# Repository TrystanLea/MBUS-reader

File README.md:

# M-Bus reader
to go with [emonTX](https://github.com/openenergymonitor/emontx3)

Part of [OpenEnergyMonitor.org](https://openenergymonitor.org) project.

This board allows you to read data from M-bus module in the heat meter. 

The Meter-Bus(M-Bus) is a low cost bus system for remote reading and powering utility meters. It is also the European Standard. 

Circuit diagram used is from [here](https://github.com/rscada/libmbus/tree/master/hardware).

The 34V is provided to the circuit through a [DC to DC voltage step up boost converter](http://www.ebay.co.uk/itm/XL6009-DC-DC-Voltage-Step-Up-Boost-Converter-replace-LM2577-3-32v-input-UK-Fast-/400858208676). 

## Schematic

## Board

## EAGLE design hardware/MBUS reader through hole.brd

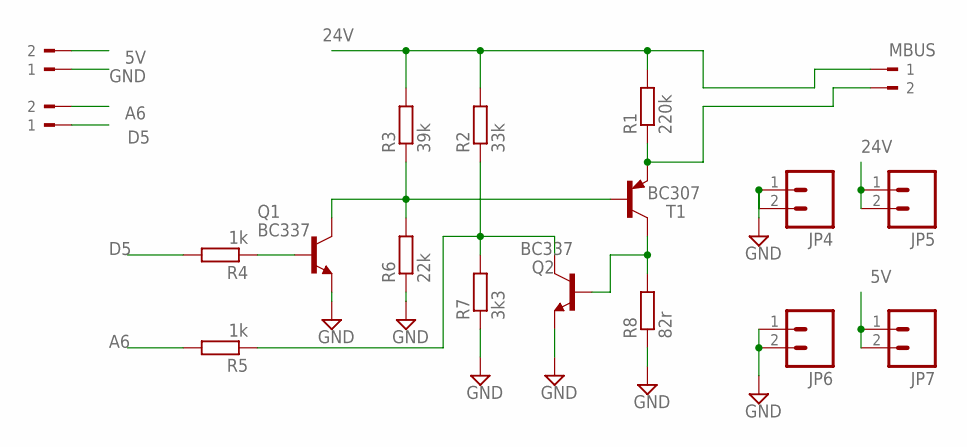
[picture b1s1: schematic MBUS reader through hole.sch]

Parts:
JP4, JP5, JP6, JP7: M02PTH; 1X02
MBUS, MBUS1, MBUS2: 180-2
Q1, Q2: BC337; TO92
R1: 220k; 0204/7
R2: 33k; 0204/7
R3: 39k; 0204/7
R4, R5: 1k; 0204/7
R6: 22k; 0204/7
R7: 3k3; 0204/7
R8: 82r; 0204/7
T1: BC307; TO92

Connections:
5V: JP7.1, JP7.2, MBUS2.2
24V: JP5.1, JP5.2, MBUS.1, R1.2, R2.2, R3.2
A6: MBUS1.2, R5.2
D5: MBUS1.1, R4.2
GND: JP4.1, JP4.2, JP6.1, JP6.2, MBUS2.1, Q1.1 (E), Q2.1 (E), R6.1, R7.1, R8.1
unnamed: MBUS.2, R1.1, T1.1 (E)
unnamed: Q2.2 (B), R8.2, T1.3 (C)
unnamed: Q1.3 (C), R3.1, R6.2, T1.2 (B)
unnamed: Q2.3 (C), R2.1, R5.1, R7.2
unnamed: Q1.2 (B), R4.1

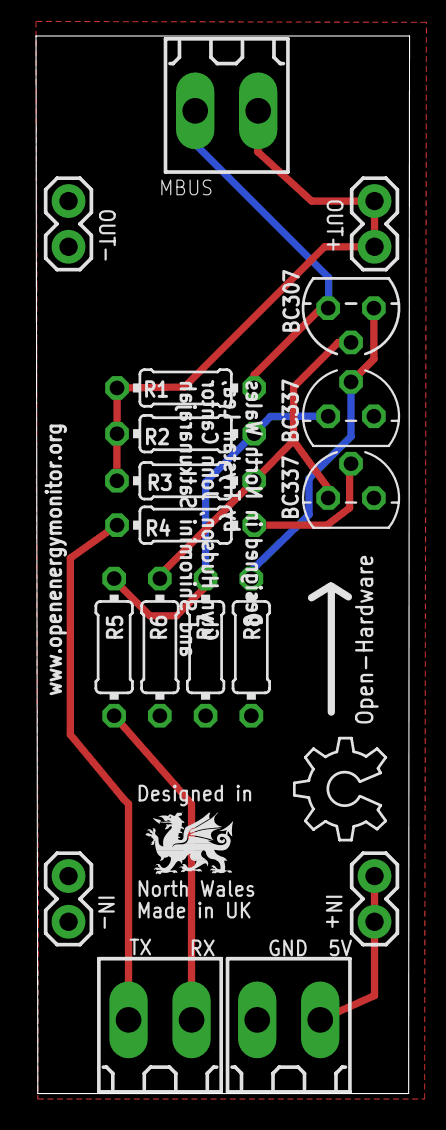
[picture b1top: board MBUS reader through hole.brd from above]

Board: 2 copper layers, 20.8 x 58.8 mm, 19 parts (0 on the bottom side), 10 nets.

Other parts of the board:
LOGO1: OSHW_LOGO_6MILX0200-NT; OSHW_6X200_NOTEXT

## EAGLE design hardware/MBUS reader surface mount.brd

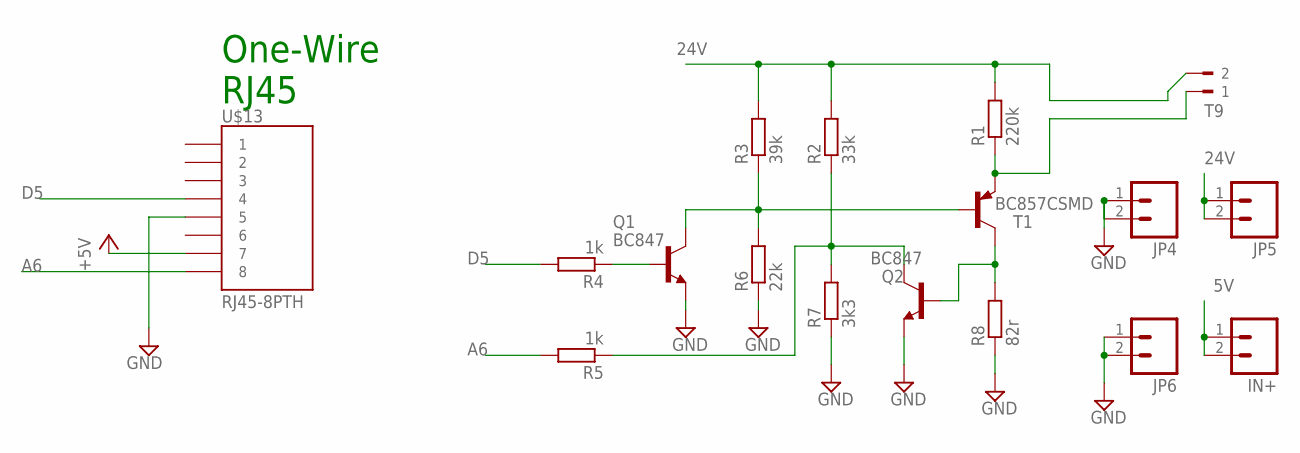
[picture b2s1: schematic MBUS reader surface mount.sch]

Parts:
IN+: M02PTH; 1X02
JP4, JP5, JP6: M02PTH; 1X02
Q1, Q2: BC847; SOT23
R1: 220k; R0603
R2: 33k; R0603
R3: 39k; R0603
R4, R5: 1k; R0603
R6: 22k; R0603
R7: 3k3; R0603
R8: 82r; R0603
T1: BC857CSMD; SOT23-BEC
T9: 180-2
U$13: RJ45-8PTH; RJ45-8

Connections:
5V: IN+.1, IN+.2, U$13.7
24V: JP5.1, JP5.2, R1.2, R2.2, R3.2, T9.2
A6: R5.2, U$13.8
D5: R4.2, U$13.4
GND: JP4.1, JP4.2, JP6.1, JP6.2, Q1.2 (E), Q2.2 (E), R6.1, R7.1, R8.1, U$13.5
unnamed: R1.1, T1.E, T9.1
unnamed: Q2.1 (B), R8.2, T1.C
unnamed: Q1.3 (C), R3.1, R6.2, T1.B
unnamed: Q2.3 (C), R2.1, R5.1, R7.2
unnamed: Q1.1 (B), R4.1

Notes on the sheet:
One-Wire RJ45

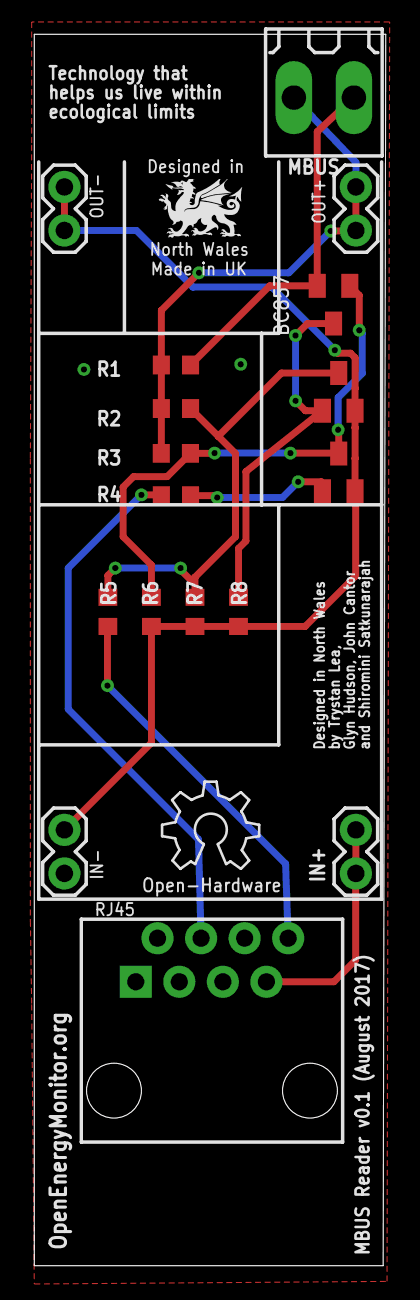
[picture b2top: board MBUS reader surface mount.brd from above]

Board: 2 copper layers, 20.5 x 71.8 mm, 18 parts (0 on the bottom side), 10 nets.

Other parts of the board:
LOGO1: OSHW_LOGO_6MILX0200-NT; OSHW_6X200_NOTEXT

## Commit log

2017-08-09 added Eagle and Gerber files
2017-08-09 Create hardware
2017-08-09 remove hardware file
2017-08-09 empty file
2017-08-09 hardware folder sorted
2017-08-16 modified files
2017-08-16 modified
2017-08-16 name changes
2017-08-18 added png files
2017-08-23 through hole with connector blocks
2017-08-23 neater

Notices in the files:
parts and their libraries:
SparkFun-Connectors: Licensing: CC v3.0 Share-Alike You are welcome to use this library for commercial purposes.
